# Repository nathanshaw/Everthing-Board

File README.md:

# Everthing-Board
The Everything Board is an Arduino shield designed to avoid having to use a breadboard to mock up quick Arduino prototypes.

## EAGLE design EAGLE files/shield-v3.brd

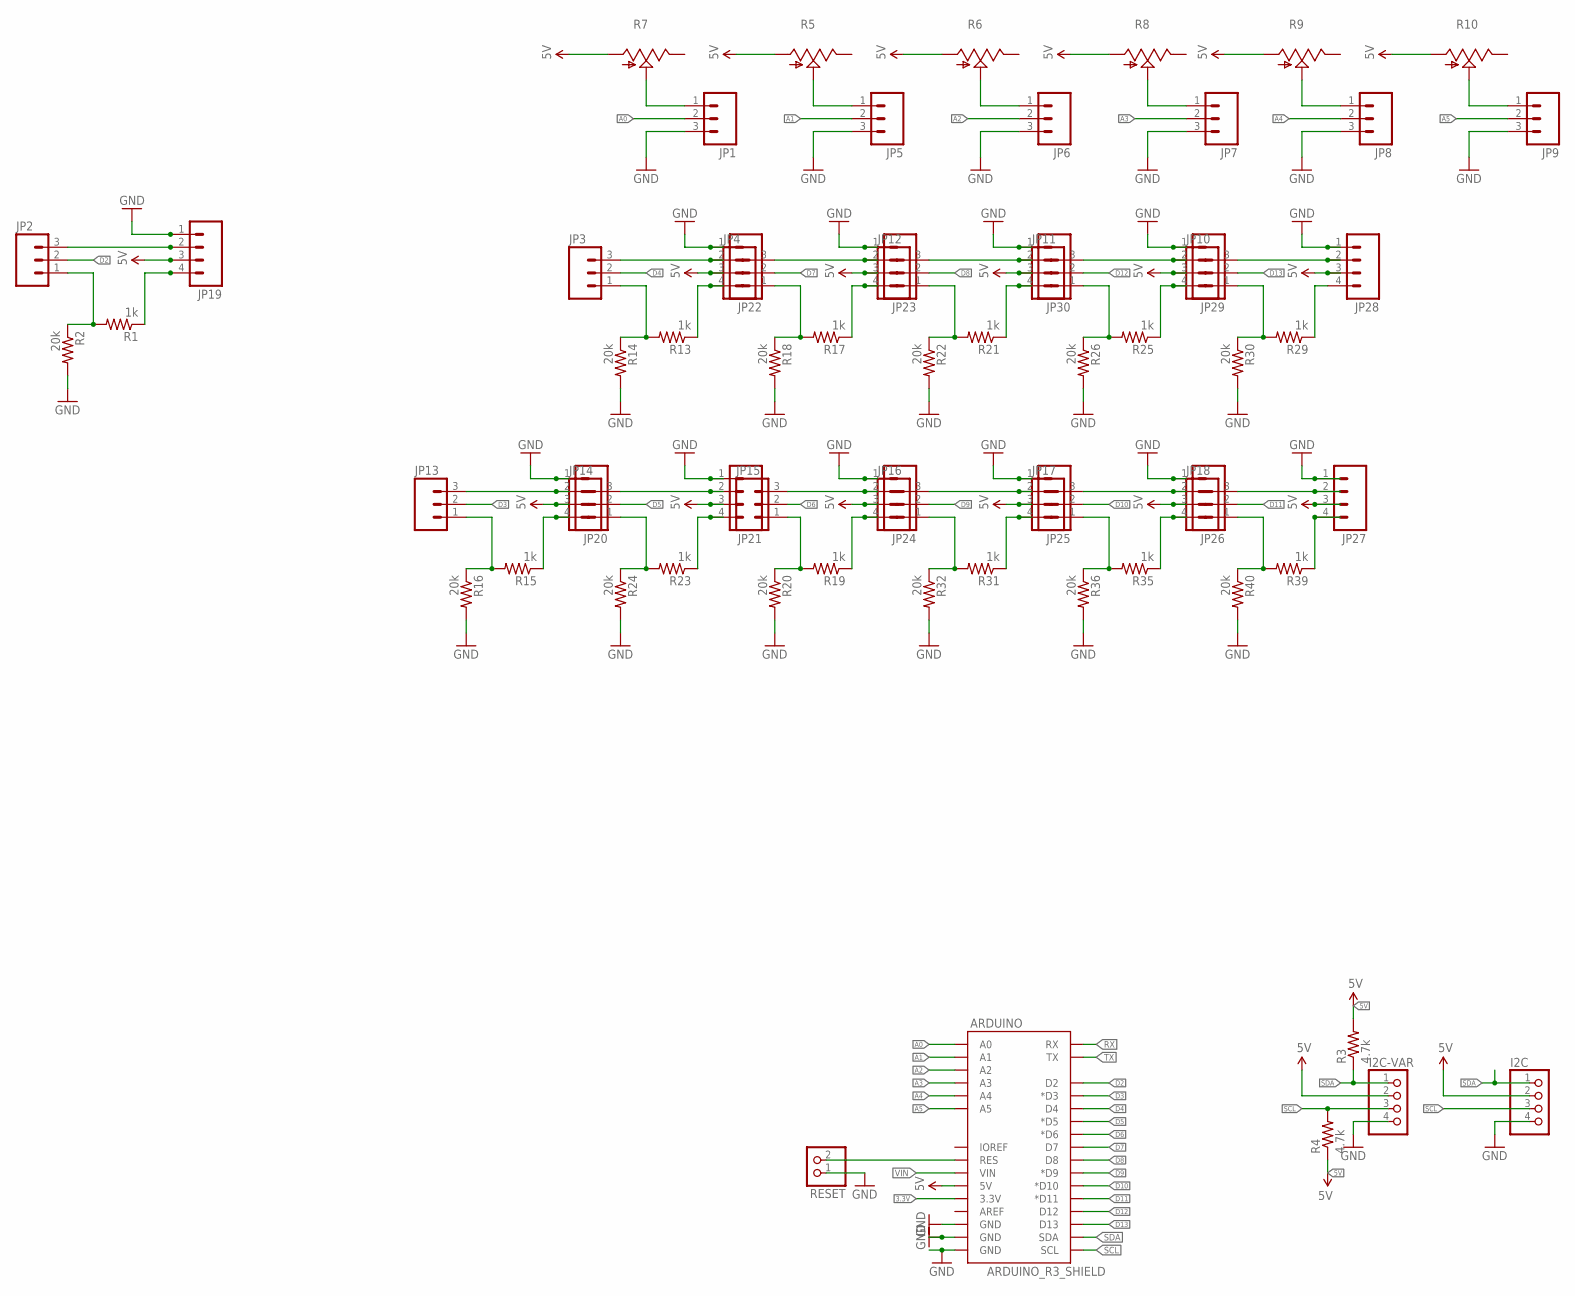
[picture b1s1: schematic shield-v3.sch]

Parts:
ARDUINO: ARDUINO_R3_SHIELD; UNO_R3_SHIELD
I2C, I2C-VAR: PINHD-1X4; 1X04
JP1, JP2, JP3, JP4, JP5, JP6, JP7, JP8, JP9, JP10, JP11, JP12, JP13, JP14, JP15, JP16, JP17, JP18: M03LOCK_NO_SILK; 1X03_LOCK_NO_SILK
JP19, JP20, JP21, JP22, JP23, JP24, JP25, JP26, JP27, JP28, JP29, JP30: M04LOCK; 1X04_LOCK
R1, R13, R15, R17, R19, R21, R23, R25, R29, R31, R35, R39: 1k; AXIAL-0.3-KIT
R2, R14, R16, R18, R20, R22, R24, R26, R30, R32, R36, R40: 20k; AXIAL-0.3-KIT
R3, R4: 4.7k; AXIAL-0.3-KIT
R5, R6, R7, R8, R9, R10: TRIM_US-CA6V; CA6V
RESET: PINHD-1X2; 1X02

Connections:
3.3V: ARDUINO.3.3V
5V: ARDUINO.5V, I2C.2, I2C-VAR.2, JP19.3, JP20.3, JP21.3, JP22.3, JP23.3, JP24.3, JP25.3, JP26.3, JP27.3, JP28.3, JP29.3, JP30.3, R3.P$2 (2), R4.P$1 (1), R5.A, R6.A, R7.A, R8.A, R9.A, R10.A
A0: ARDUINO.A0, JP1.2
A1: ARDUINO.A1, JP5.2
A2: ARDUINO.A2, JP6.2
A3: ARDUINO.A3, JP7.2
A4: ARDUINO.A4, JP8.2
A5: ARDUINO.A5, JP9.2
D2: ARDUINO.D2, JP2.2
D3: ARDUINO.D3 (*D3), JP13.2
D4: ARDUINO.D4, JP3.2
D5: ARDUINO.D5 (*D5), JP14.2
D6: ARDUINO.D6 (*D6), JP15.2
D7: ARDUINO.D7, JP4.2
D8: ARDUINO.D8, JP12.2
D9: ARDUINO.D9 (*D9), JP16.2
D10: ARDUINO.D10 (*D10), JP17.2
D11: ARDUINO.D11 (*D11), JP18.2
D12: ARDUINO.D12, JP11.2
D13: ARDUINO.D13, JP10.2
GND: ARDUINO.GND@0 (GND), ARDUINO.GND@1 (GND), ARDUINO.GND@2 (GND), I2C.4, I2C-VAR.4, JP1.3, JP5.3, JP6.3, JP7.3, JP8.3, JP9.3, JP19.1, JP20.1, JP21.1, JP22.1, JP23.1, JP24.1, JP25.1, JP26.1, JP27.1, JP28.1, JP29.1, JP30.1, R2.P$2 (2), R14.P$2 (2), R16.P$2 (2), R18.P$2 (2), R20.P$2 (2), R22.P$2 (2), R24.P$2 (2), R26.P$2 (2), R30.P$2 (2), R32.P$2 (2), R36.P$2 (2), R40.P$2 (2), RESET.1
unnamed: ARDUINO.RES, RESET.2
unnamed: JP1.1, R7.S
unnamed: JP5.1, R5.S
unnamed: JP6.1, R6.S
unnamed: JP7.1, R8.S
unnamed: JP8.1, R9.S
unnamed: JP9.1, R10.S
unnamed: JP19.4, R1.P$1 (1)
unnamed: JP2.3, JP19.2
unnamed: JP2.1, R1.P$2 (2), R2.P$1 (1)
unnamed: JP22.4, R13.P$1 (1)
unnamed: JP3.3, JP22.2
unnamed: JP3.1, R13.P$2 (2), R14.P$1 (1)
unnamed: JP20.4, R15.P$1 (1)
unnamed: JP13.3, JP20.2
unnamed: JP13.1, R15.P$2 (2), R16.P$1 (1)
unnamed: JP23.4, R17.P$1 (1)
unnamed: JP4.3, JP23.2
unnamed: JP4.1, R17.P$2 (2), R18.P$1 (1)
unnamed: JP24.4, R19.P$1 (1)
unnamed: JP15.3, JP24.2
unnamed: JP15.1, R19.P$2 (2), R20.P$1 (1)
unnamed: JP30.4, R21.P$1 (1)
unnamed: JP12.3, JP30.2
unnamed: JP12.1, R21.P$2 (2), R22.P$1 (1)
unnamed: JP21.4, R23.P$1 (1)
unnamed: JP14.3, JP21.2
unnamed: JP14.1, R23.P$2 (2), R24.P$1 (1)
unnamed: JP29.4, R25.P$1 (1)
unnamed: JP11.3, JP29.2
unnamed: JP11.1, R25.P$2 (2), R26.P$1 (1)
unnamed: JP28.4, R29.P$1 (1)
unnamed: JP10.3, JP28.2
unnamed: JP10.1, R29.P$2 (2), R30.P$1 (1)
unnamed: JP25.4, R31.P$1 (1)
unnamed: JP16.3, JP25.2
unnamed: JP16.1, R31.P$2 (2), R32.P$1 (1)
unnamed: JP26.4, R35.P$1 (1)
unnamed: JP17.3, JP26.2
unnamed: JP17.1, R35.P$2 (2), R36.P$1 (1)
unnamed: JP27.4, R39.P$1 (1)
unnamed: JP18.3, JP27.2
unnamed: JP18.1, R39.P$2 (2), R40.P$1 (1)
RX: ARDUINO.RX
SCL: ARDUINO.SCL, I2C.3, I2C-VAR.3, R4.P$2 (2)
SDA: ARDUINO.SDA, I2C.1, I2C-VAR.1, R3.P$1 (1)
TX: ARDUINO.TX
VIN: ARDUINO.VIN

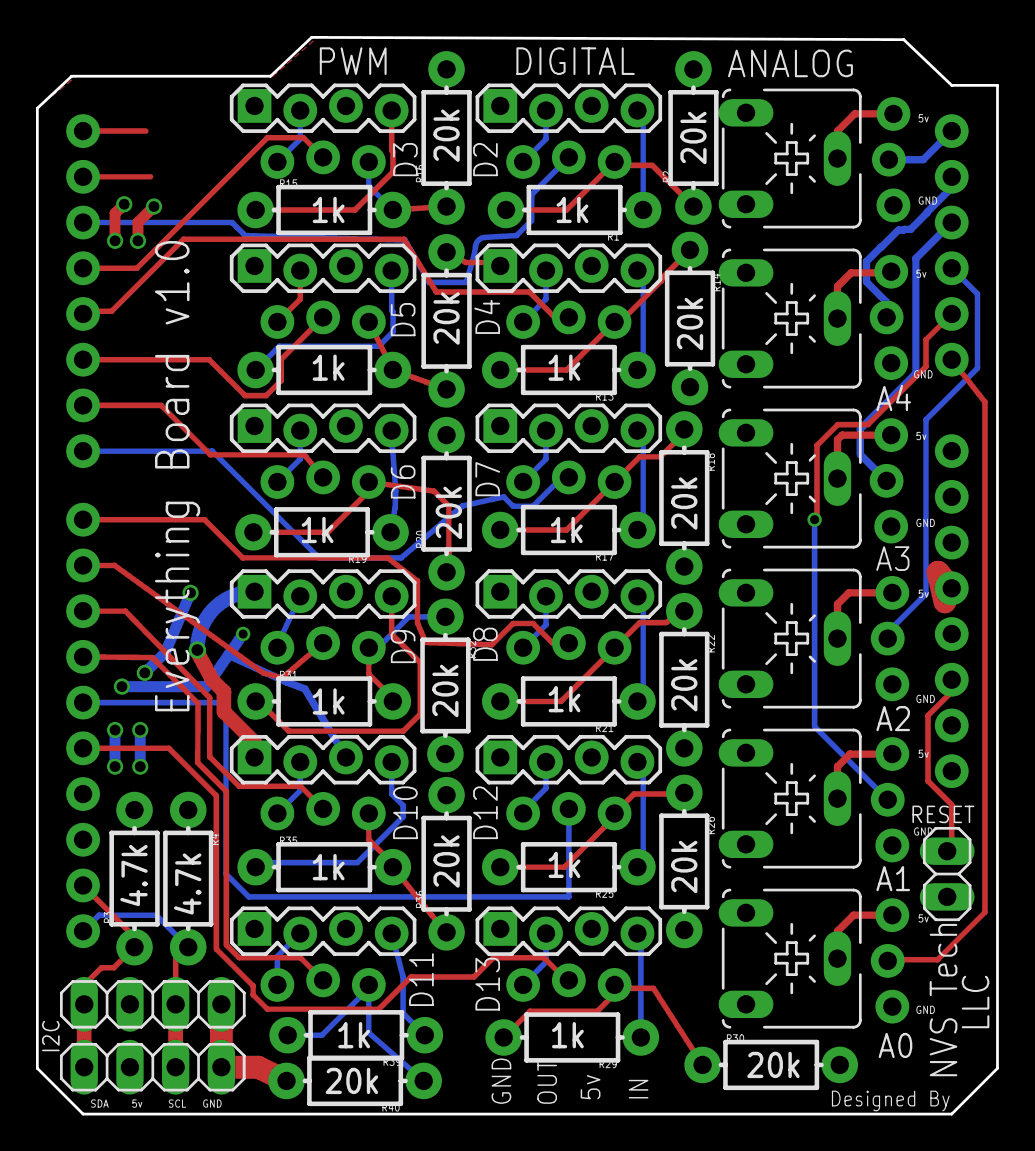
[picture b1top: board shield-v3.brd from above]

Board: 2 copper layers, 53.3 x 59.8 mm, 66 parts (0 on the bottom side), 65 nets.

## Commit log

2018-07-24 added eagle files along with the .pdf explaining what is what

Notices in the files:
parts and their libraries:
Nathans-Arduinos: Licensing: Creative Commons ShareAlike 4.0 International - https://creativecommons.org/licenses/by-sa/4.0
